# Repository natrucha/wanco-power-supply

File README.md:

# wanco-power-supply
Eagle files for the power supply PCB

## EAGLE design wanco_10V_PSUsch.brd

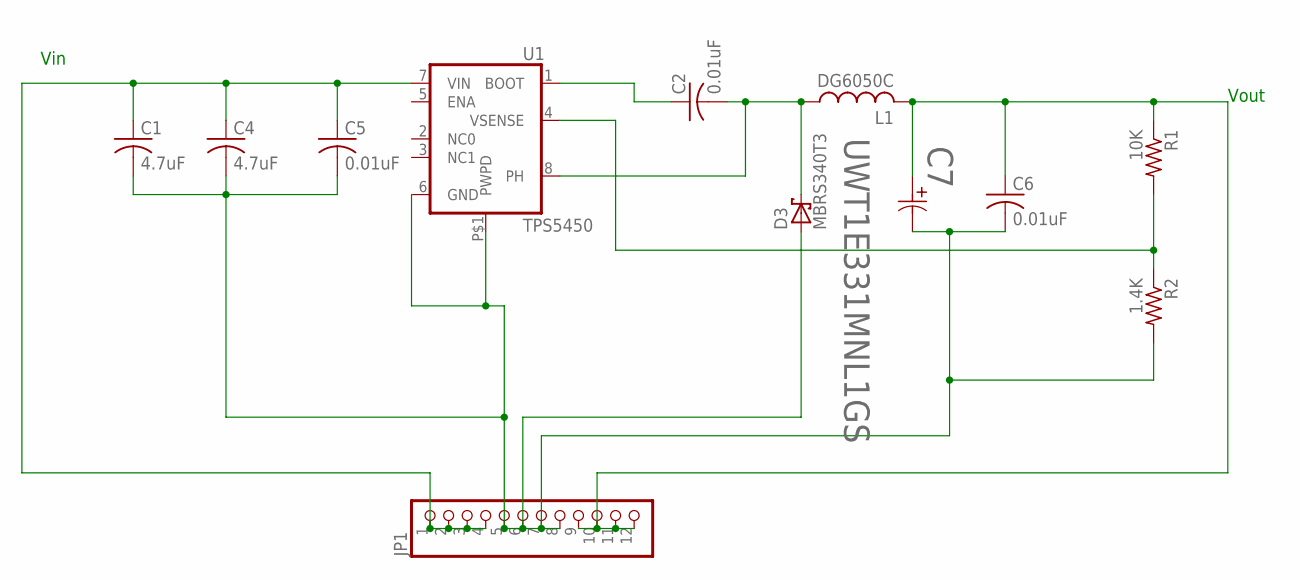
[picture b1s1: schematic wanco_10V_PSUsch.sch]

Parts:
C1, C4: 4.7uF; C1206
C2, C5, C6: 0.01uF; C0805
C7: UWT1E331MNL1GS; PCAP_8X10-ELECT
D3: MBRS340T3; SMC
JP1: PINHD-1X12; 1X12
L1: DG6050C; DG
R1: 10K; R0805
R2: 1.4K; R0805
U1: TPS5450; SO08

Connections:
BOOT: C2.1, U1.1 (BOOT)
GND: C1.2, C4.2, C5.2, C6.2, C7.2 (22), D3.A, JP1.5, JP1.6, JP1.7, JP1.8, R2.2, U1.6 (GND), U1.P$1 (PWPD)
PH: C2.2, D3.C, L1.P$1 (1), U1.8 (PH)
VIN: C1.1, C4.1, C5.1, JP1.1, JP1.2, JP1.3, JP1.4, U1.7 (VIN)
VOUT: C6.1, C7.1 (11), JP1.9, JP1.10, JP1.11, JP1.12, L1.P$2 (2), R1.1
VSENSE: R1.2, R2.1, U1.4 (VSENSE)

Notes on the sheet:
Vout
Vin

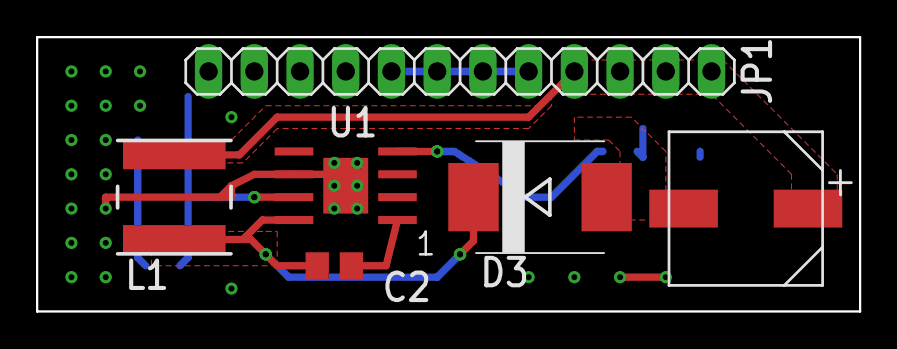
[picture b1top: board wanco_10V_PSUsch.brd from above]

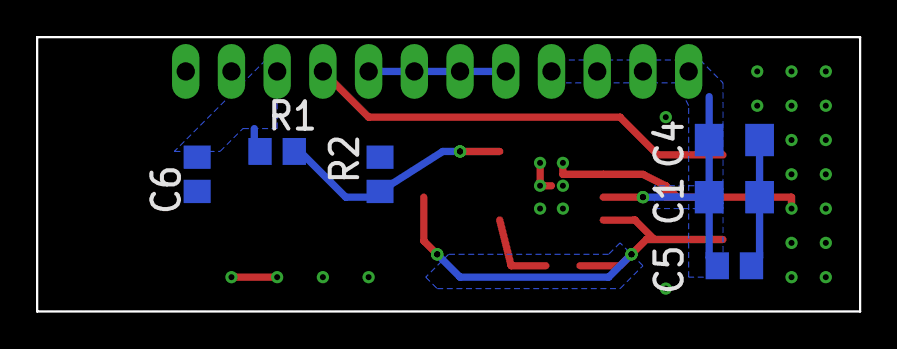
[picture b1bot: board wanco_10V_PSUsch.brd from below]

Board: 2 copper layers, 45.7 x 15.2 mm, 12 parts (6 on the bottom side), 6 nets.

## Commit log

2017-07-17 final board project files

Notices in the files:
parts and their libraries:
COPYRIGHT: Copyright (C) 2015 Accelerated Designs. All rights reserved
